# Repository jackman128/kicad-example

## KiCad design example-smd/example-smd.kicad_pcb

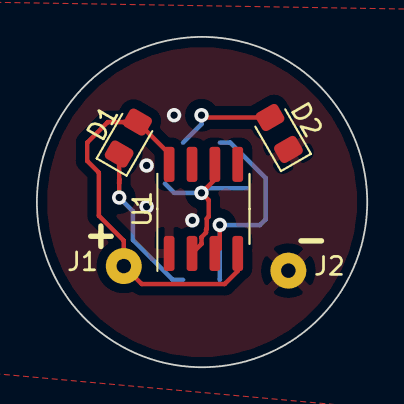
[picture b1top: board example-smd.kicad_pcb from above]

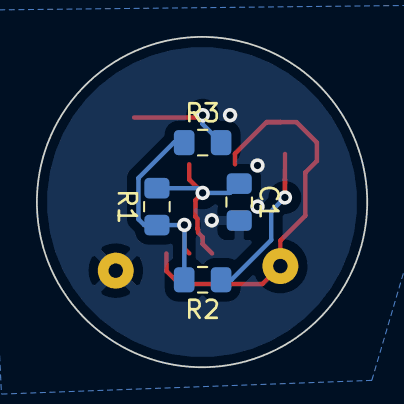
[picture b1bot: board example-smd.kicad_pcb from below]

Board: 2 copper layers, 18.4 x 18.4 mm, 9 parts (4 on the bottom side), 6 nets.

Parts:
C1: 10u; C_0805_2012Metric_Pad1.15x1.40mm_HandSolder
D1, D2: LED; LED_0805_2012Metric_Pad1.15x1.40mm_HandSolder
J1, J2: Conn_01x01; SolderWirePad_1x01_Drill0.8mm
R1: 47k; R_0805_2012Metric_Pad1.15x1.40mm_HandSolder
R2, R3: 470; R_0805_2012Metric_Pad1.15x1.40mm_HandSolder
U1: NE555; SOIC-8_3.9x4.9mm_P1.27mm

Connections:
+9V: D1.2, J1.1, U1.4, U1.8
GND: C1.2, D2.1, J2.1, U1.1
unnamed: C1.1, R1.2, U1.2, U1.6
unnamed: D1.1, R2.1
unnamed: D2.2, R3.2
unnamed: R1.1, R2.2, R3.1, U1.3

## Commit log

2020-01-24 THT done, SMD almost done.
2020-01-25 Both THT and SMD done.
